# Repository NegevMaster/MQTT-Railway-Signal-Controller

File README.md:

# MQTT Railway Signal Controller

A PlatformIO firmware project for an ESP32-based railway signal controller that drives multiple signal mast layouts over MQTT.

## Overview

This project listens for MQTT commands and updates railway signal lamps connected to PCA9685 boards. It is designed for a modular signal setup with support for standard signal states and distant-signal combinations.

## Features

- ESP32 firmware using Arduino/PlatformIO
- Wi-Fi + MQTT control
- PCA9685 PWM signal board support
- Flashing and steady LED states
- Signal status handling for main and distant signals
- Clean local configuration override for Wi‑Fi and MQTT credentials

## Hardware

- ESP32 development board
- One or more PCA9685 I2C PWM controllers
- Railway signal LEDs or LED modules on the PCA9685 outputs
- Wi‑Fi network and MQTT broker

## Repository layout

- `src/` – firmware entry points and signal logic
- `include/` – shared configuration and declarations
- `lib/` – project libraries (if added later)
- `test/` – test scaffolding
- `platformio.ini` – PlatformIO build configuration

## Setup

1. Copy the sample config file:
   ```bash
   copy include\config.local.h.example include\config.local.h
   ```
2. Edit `include/config.local.h` and fill in your local Wi‑Fi and MQTT values.
3. Build and upload:
   ```bash
   pio run -e esp32dev
   pio run -e esp32dev -t upload
   ```
4. Optionally monitor serial output:
   ```bash
   pio device monitor -e esp32dev
   ```

## MQTT topic structure

The firmware subscribes to topics under the base prefix defined in `config.h`:

```cpp
#define BASE_MQTT_TOPIC "trains/track/signalmast/"
```

Messages are expected to include the signal name and a display state such as `Sygnał S1`, `Sygnał S2`, and similar values used by the project.

## Security note

This repository intentionally does not include real credentials. Keep your personal Wi‑Fi and MQTT settings in `include/config.local.h`, which is ignored by Git.

## License

This project is licensed under the MIT License. See [LICENSE](LICENSE) for details.

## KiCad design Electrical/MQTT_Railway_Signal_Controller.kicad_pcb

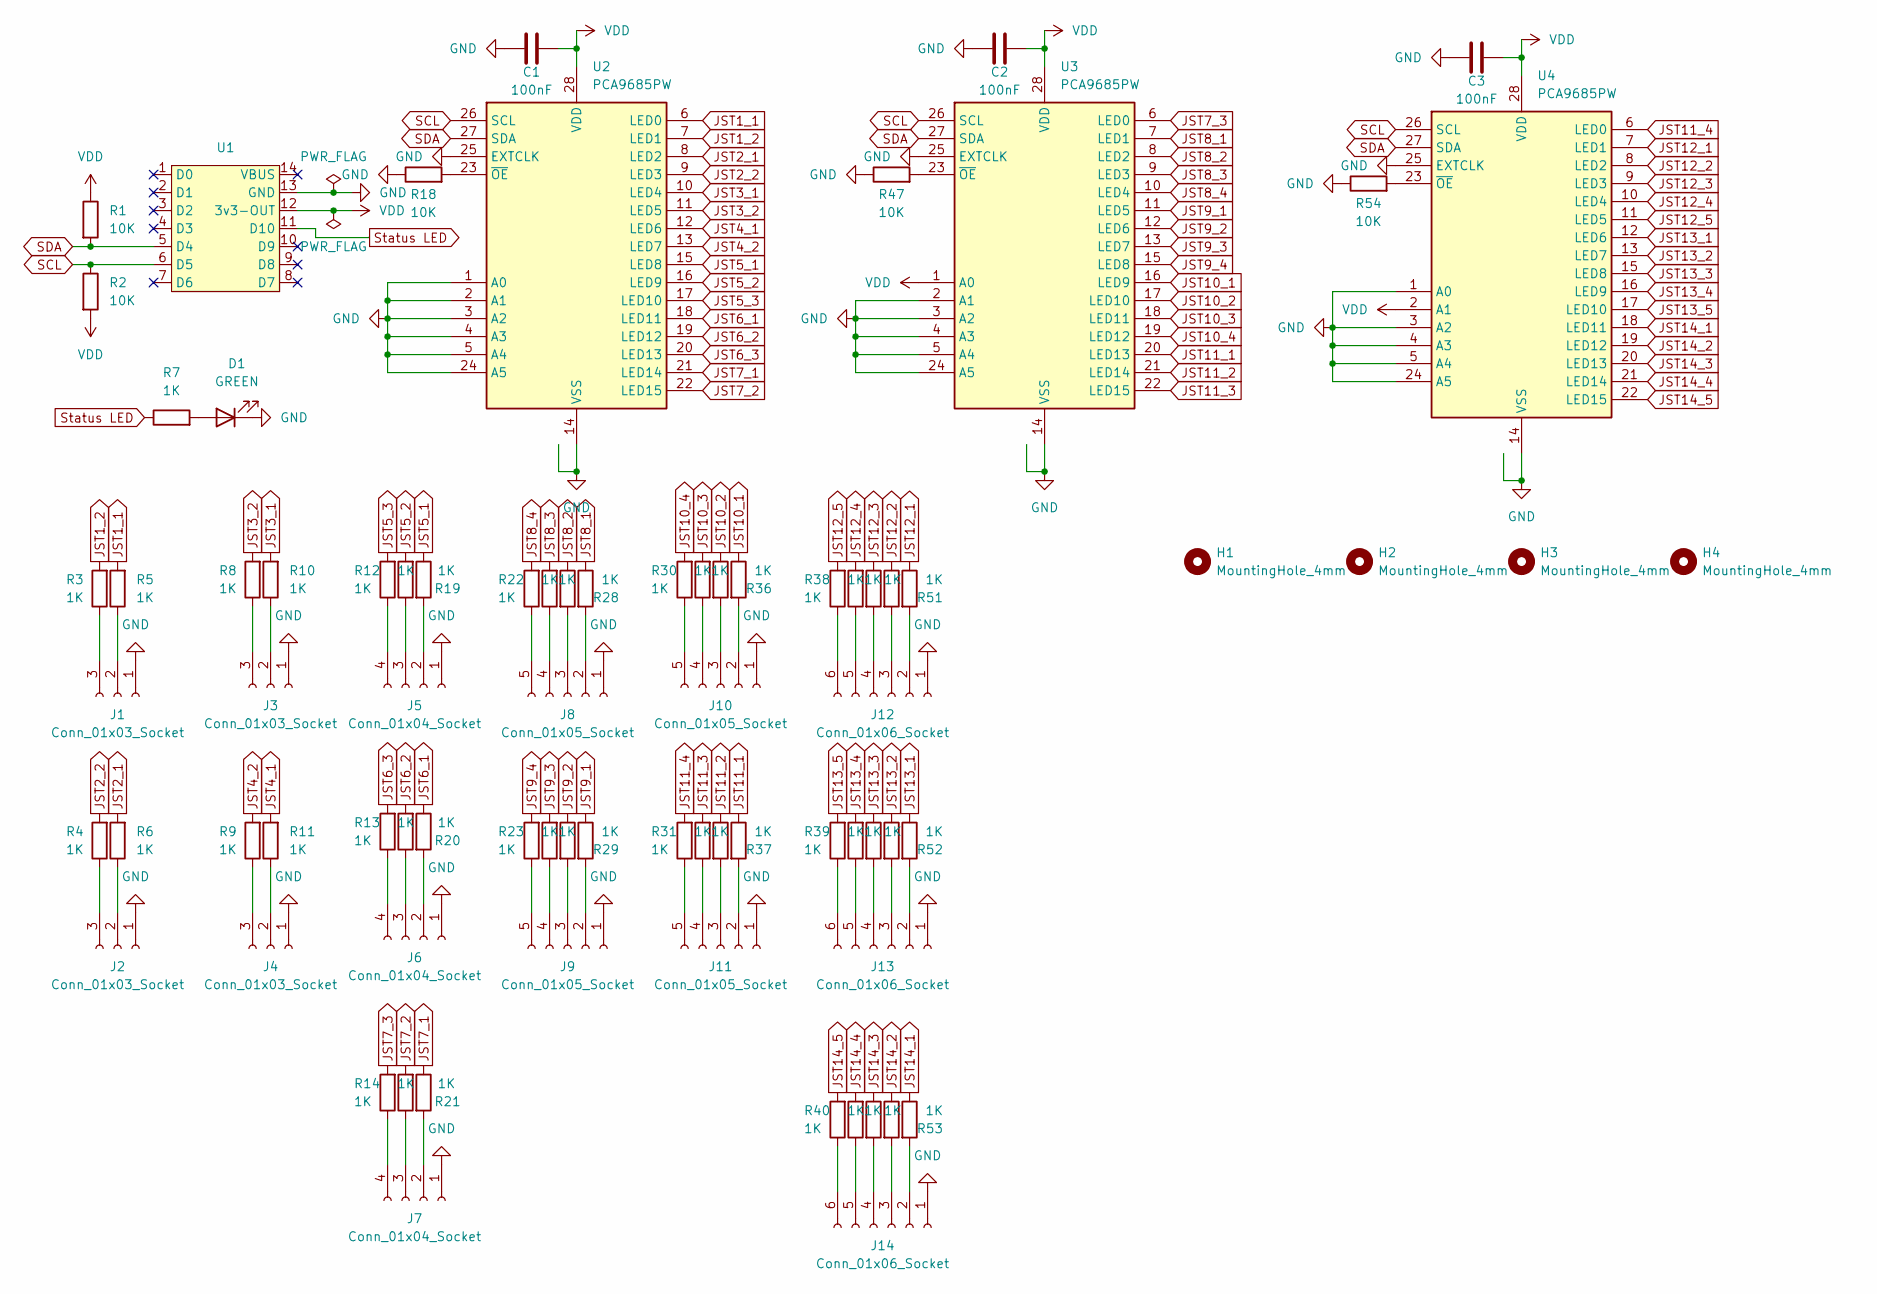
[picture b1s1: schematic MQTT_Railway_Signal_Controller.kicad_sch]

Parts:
C1, C2, C3: 100nF; C_0805_2012Metric
D1: GREEN; LED_D3.0mm_FlatTop
H1, H2, H3, H4: MountingHole_4mm
J1, J2, J3, J4: Conn_01x03_Socket; JST_XH_B3B-XH-A_1x03_P2.50mm_Vertical
J5, J6, J7: Conn_01x04_Socket; JST_XH_B4B-XH-A_1x04_P2.50mm_Vertical
J8, J9, J10, J11: Conn_01x05_Socket; JST_XH_B5B-XH-A_1x05_P2.50mm_Vertical
J12, J13, J14: Conn_01x06_Socket; JST_XH_B6B-XH-A_1x06_P2.50mm_Vertical
R1, R2, R18, R47, R54: 10K; R_0805_2012Metric
R3, R4, R5, R6, R7, R8, R9, R10, R11, R12, R13, R14, R15, R16, R17, R19, R20, R21, R22, R23, R24, R25, R26, R27, R28, R29, R30, R31, R32, R33, R34, R35, R36, R37, R38, R39, R40, R41, R42, R43, R44, R45, R46, R48, R49, R50, R51, R52, R53: 1K; R_0805_2012Metric
U1: MCU_Seeed_ESP32C3
U2, U3, U4: PCA9685PW; TSSOP-28_4.4x9.7mm_P0.65mm

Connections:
GND: C1.1, C2.1, C3.1, D1.1 (K), J1.1, J2.1, J3.1, J4.1, J5.1, J6.1, J7.1, J8.1, J9.1, J10.1, J11.1, J12.1, J13.1, J14.1, R18.1, R47.1, R54.1, U1.13 (GND), U2.1 (A0), U2.2 (A1), U2.3 (A2), U2.4 (A3), U2.5 (A4), U2.14 (VSS), U2.24 (A5), U2.25 (EXTCLK), U3.2 (A1), U3.3 (A2), U3.4 (A3), U3.5 (A4), U3.14 (VSS), U3.24 (A5), U3.25 (EXTCLK), U4.1 (A0), U4.3 (A2), U4.4 (A3), U4.5 (A4), U4.14 (VSS), U4.24 (A5), U4.25 (EXTCLK)
JST1_1: R5.2, U2.6 (LED0)
JST1_2: R3.2, U2.7 (LED1)
JST2_1: R6.2, U2.8 (LED2)
JST2_2: R4.2, U2.9 (LED3)
JST3_1: R10.2, U2.10 (LED4)
JST3_2: R8.2, U2.11 (LED5)
JST4_1: R11.2, U2.12 (LED6)
JST4_2: R9.2, U2.13 (LED7)
JST5_1: R19.1, U2.15 (LED8)
JST5_2: R15.2, U2.16 (LED9)
JST5_3: R12.2, U2.17 (LED10)
JST6_1: R20.1, U2.18 (LED11)
JST6_2: R16.2, U2.19 (LED12)
JST6_3: R13.2, U2.20 (LED13)
JST7_1: R21.1, U2.21 (LED14)
JST7_2: R17.2, U2.22 (LED15)
JST7_3: R14.2, U3.6 (LED0)
JST8_1: R28.1, U3.7 (LED1)
JST8_2: R26.1, U3.8 (LED2)
JST8_3: R24.2, U3.9 (LED3)
JST8_4: R22.2, U3.10 (LED4)
JST9_1: R29.1, U3.11 (LED5)
JST9_2: R27.1, U3.12 (LED6)
JST9_3: R25.2, U3.13 (LED7)
JST9_4: R23.2, U3.15 (LED8)
JST10_1: R36.1, U3.16 (LED9)
JST10_2: R34.1, U3.17 (LED10)
JST10_3: R32.2, U3.18 (LED11)
JST10_4: R30.2, U3.19 (LED12)
JST11_1: R37.1, U3.20 (LED13)
JST11_2: R35.1, U3.21 (LED14)
JST11_3: R33.2, U3.22 (LED15)
JST11_4: R31.2, U4.6 (LED0)
JST12_1: R51.1, U4.7 (LED1)
JST12_2: R48.1, U4.8 (LED2)
JST12_3: R44.1, U4.9 (LED3)
JST12_4: R41.2, U4.10 (LED4)
JST12_5: R38.2, U4.11 (LED5)
JST13_1: R52.1, U4.12 (LED6)
JST13_2: R49.1, U4.13 (LED7)
JST13_3: R45.1, U4.15 (LED8)
JST13_4: R42.2, U4.16 (LED9)
JST13_5: R39.2, U4.17 (LED10)
JST14_1: R53.1, U4.18 (LED11)
JST14_2: R50.1, U4.19 (LED12)
JST14_3: R46.1, U4.20 (LED13)
JST14_4: R43.2, U4.21 (LED14)
JST14_5: R40.2, U4.22 (LED15)
unnamed: D1.2 (A), R7.2
unnamed: J1.2, R5.1
unnamed: J1.3, R3.1
unnamed: J2.2, R6.1
unnamed: J2.3, R4.1
unnamed: J3.2, R10.1
unnamed: J3.3, R8.1
unnamed: J4.2, R11.1
unnamed: J4.3, R9.1
unnamed: J5.2, R19.2
unnamed: J5.3, R15.1
unnamed: J5.4, R12.1
unnamed: J6.2, R20.2
unnamed: J6.3, R16.1
unnamed: J6.4, R13.1
unnamed: J7.2, R21.2
unnamed: J7.3, R17.1
unnamed: J7.4, R14.1
unnamed: J8.2, R28.2
unnamed: J8.3, R26.2
unnamed: J8.4, R24.1
unnamed: J8.5, R22.1
unnamed: J9.2, R29.2
unnamed: J9.3, R27.2
unnamed: J9.4, R25.1
unnamed: J9.5, R23.1
unnamed: J10.2, R36.2
unnamed: J10.3, R34.2
unnamed: J10.4, R32.1
unnamed: J10.5, R30.1
unnamed: J11.2, R37.2
unnamed: J11.3, R35.2
unnamed: J11.4, R33.1
unnamed: J11.5, R31.1
unnamed: J12.2, R51.2
unnamed: J12.3, R48.2
unnamed: J12.4, R44.2
unnamed: J12.5, R41.1
unnamed: J12.6, R38.1
unnamed: J13.2, R52.2
unnamed: J13.3, R49.2
unnamed: J13.4, R45.2
unnamed: J13.5, R42.1
unnamed: J13.6, R39.1
unnamed: J14.2, R53.2
unnamed: J14.3, R50.2
unnamed: J14.4, R46.2
unnamed: J14.5, R43.1
unnamed: J14.6, R40.1
unnamed: R18.2, U2.23 (~OE)
unnamed: R47.2, U3.23 (~OE)
unnamed: R54.2, U4.23 (~OE)
SCL: R2.1, U1.6 (D5), U2.26 (SCL), U3.26 (SCL), U4.26 (SCL)
SDA: R1.2, U1.5 (D4), U2.27 (SDA), U3.27 (SDA), U4.27 (SDA)
Status LED: R7.1, U1.11 (D10)
VDD: C1.2, C2.2, C3.2, R1.1, R2.2, U1.12 (3v3-OUT), U2.28 (VDD), U3.1 (A0), U3.28 (VDD), U4.2 (A1), U4.28 (VDD)

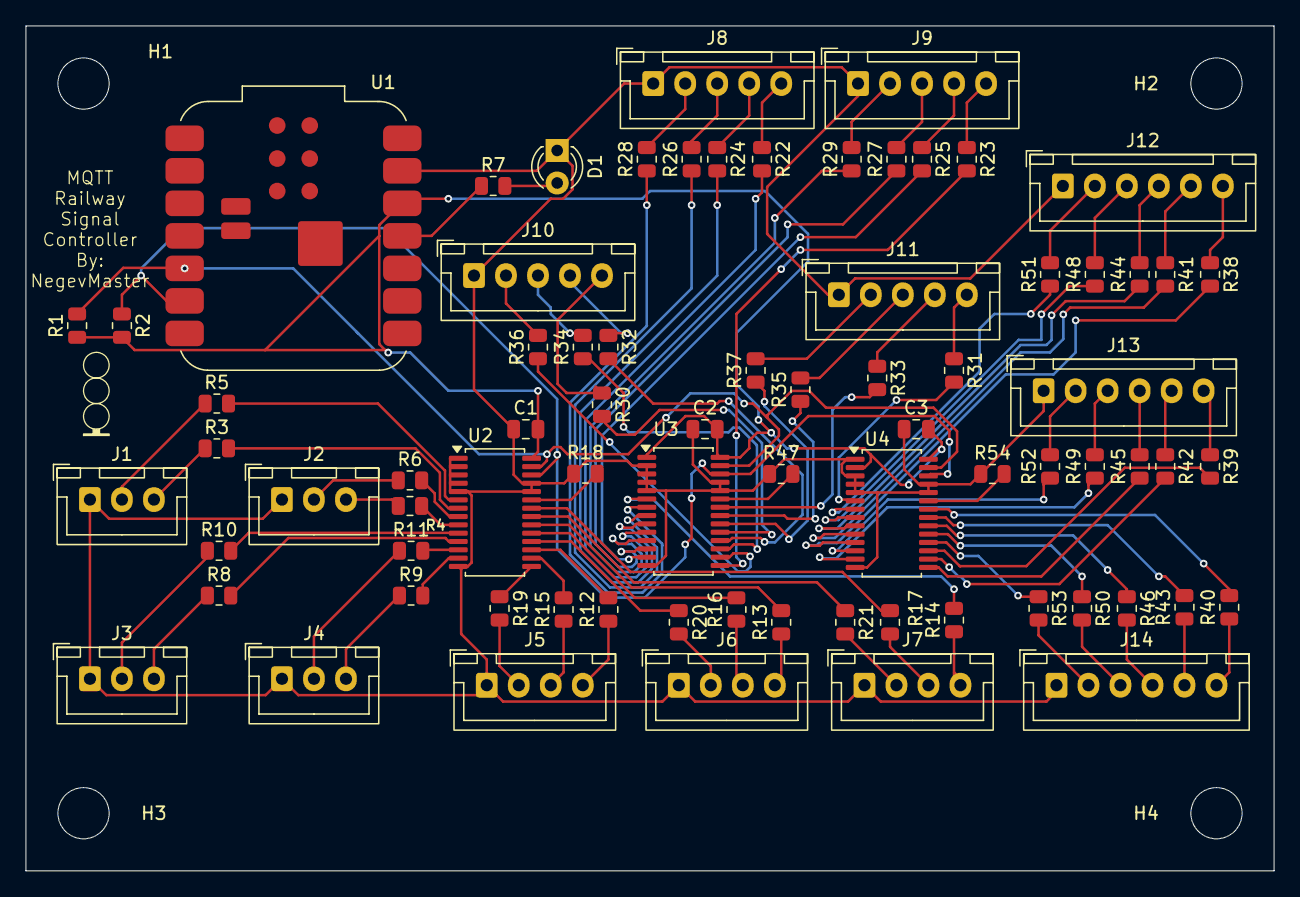
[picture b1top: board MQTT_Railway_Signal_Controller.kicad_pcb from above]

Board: 2 copper layers, 97.5 x 66.0 mm, 80 parts (0 on the bottom side), 105 nets.

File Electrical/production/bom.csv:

Designator,Footprint,Quantity,Value,LCSC Part #
"C1, C2, C3",0805,3,100nF,
D1,LED_D3.0mm_FlatTop,1,GREEN,
"J1, J2, J3, J4",JST_XH_B3B-XH-A_1x03_P2.50mm_Vertical,4,Conn_01x03_Socket,
"J10, J11, J8, J9",JST_XH_B5B-XH-A_1x05_P2.50mm_Vertical,4,Conn_01x05_Socket,
"J12, J13, J14",JST_XH_B6B-XH-A_1x06_P2.50mm_Vertical,3,Conn_01x06_Socket,
"J5, J6, J7",JST_XH_B4B-XH-A_1x04_P2.50mm_Vertical,3,Conn_01x04_Socket,
"R1, R18, R2, R47, R54",0805,5,10K,
"R10, R11, R12, R13, R14, R15, R16, R17, R19, R20, R21, R22, R23, R24, R25, R26, R27, R28, R29, R3, R30, R31, R32, R33, R34, R35, R36, R37, R38, R39, R4, R40, R41, R42, R43, R44, R45, R46, R48, R49, R5, R50, R51, R52, R53, R6, R7, R8, R9",0805,49,1K,
U1,MCU_Seeed_ESP32C3,1,~,
"U2, U3, U4",TSSOP-28_4.4x9.7mm_P0.65mm,3,PCA9685PW,
